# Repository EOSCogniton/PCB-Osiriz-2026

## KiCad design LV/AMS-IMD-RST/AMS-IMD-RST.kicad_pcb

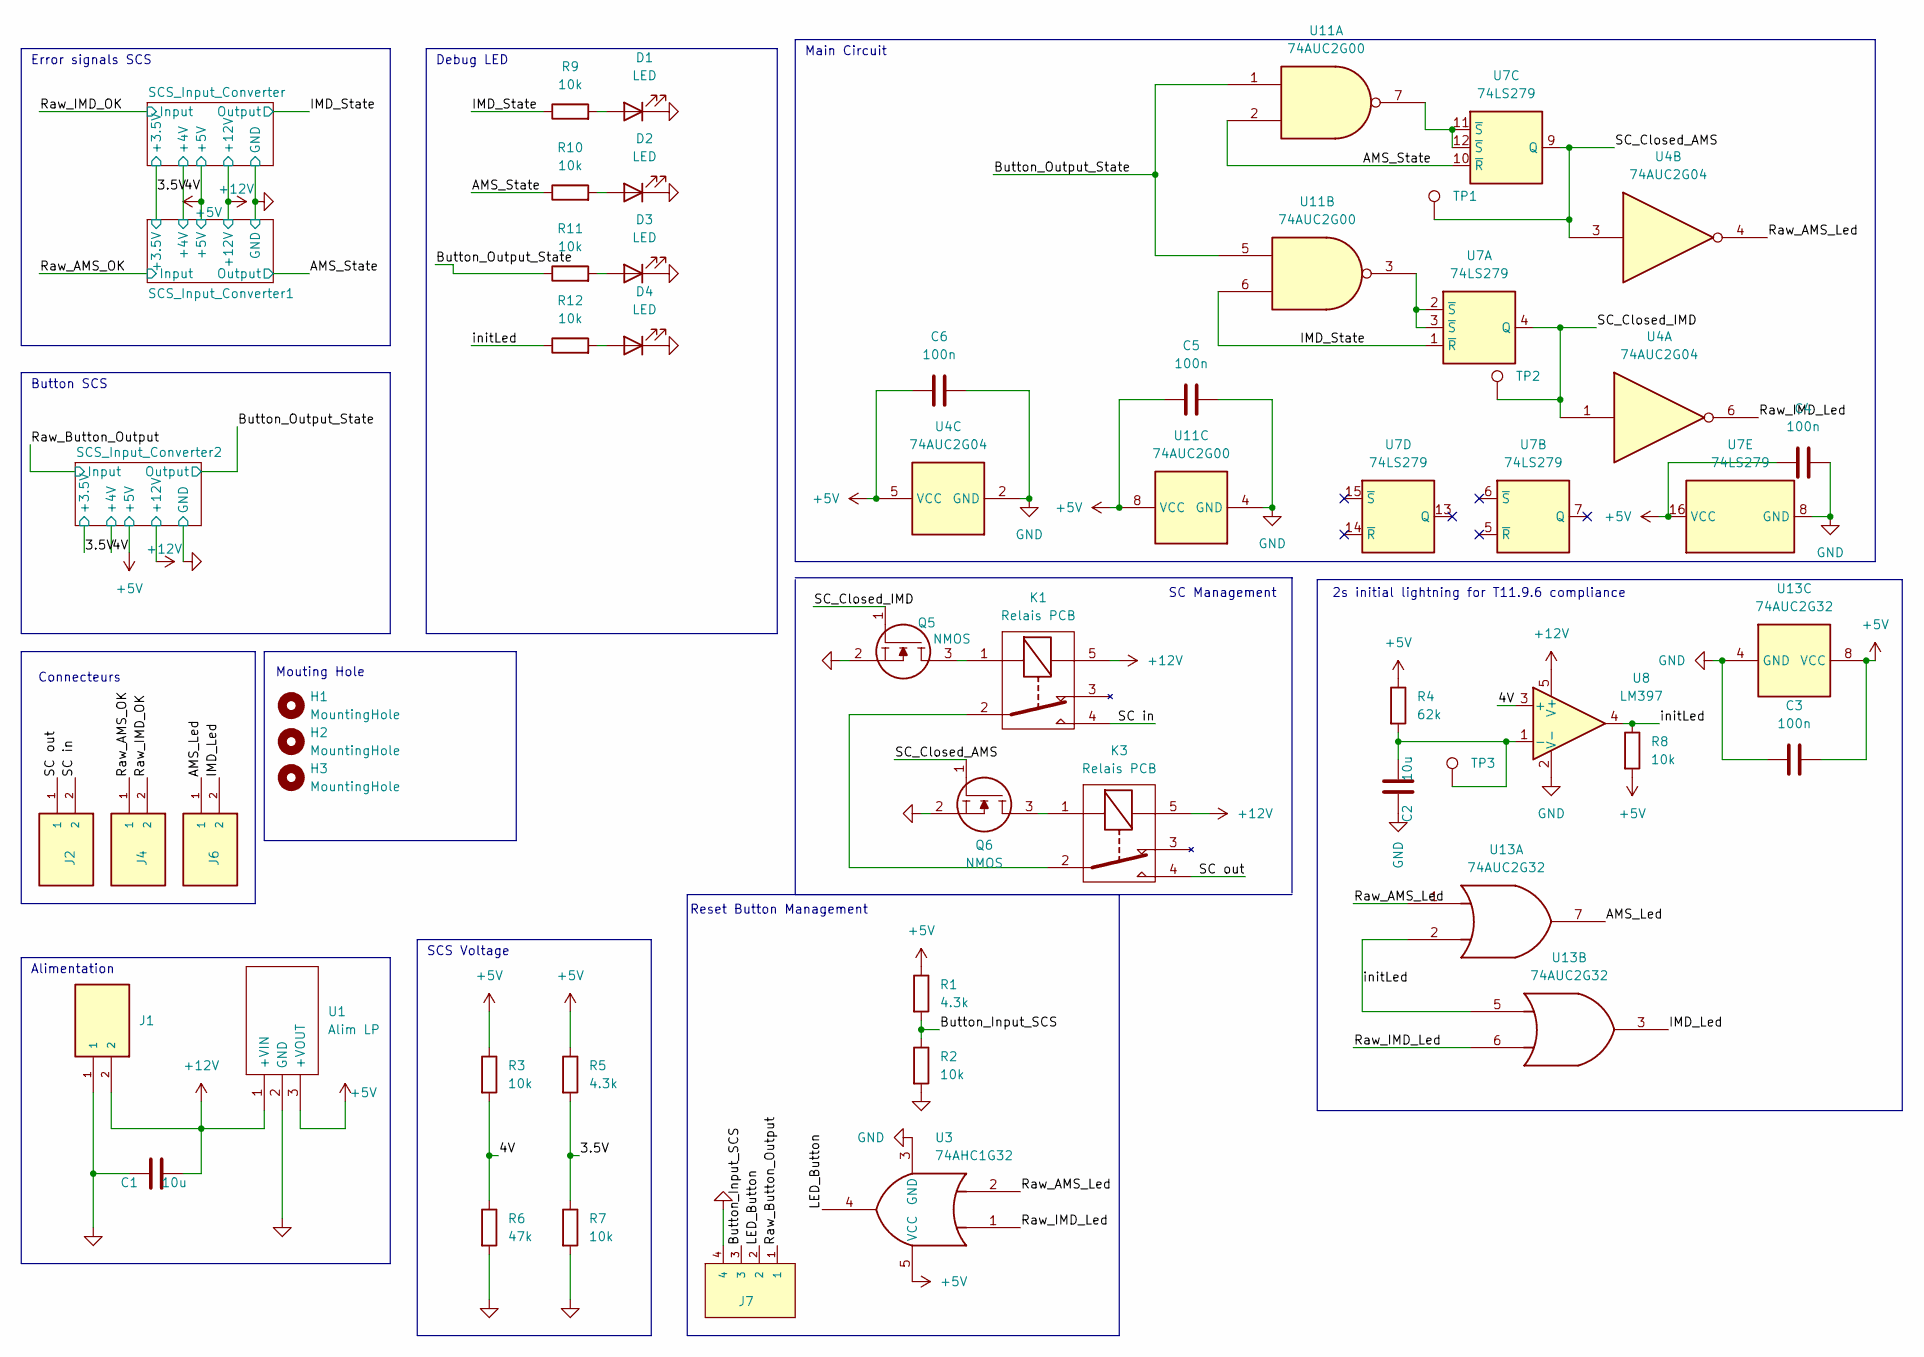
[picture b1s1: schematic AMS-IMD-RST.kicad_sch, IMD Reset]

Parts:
C1, C2: 10u; CP_Radial_D5.0mm_P2.00mm
C3, C4, C5, C6: 100n; C_0805_2012Metric_Pad1.18x1.45mm_HandSolder
D1, D2, D3, D4: LED; LED_D3.0mm
H1, H2, H3: MountingHole; MountingHole_2.7mm_M2.5
J1, J2, J4, J6: 2P Droit 2-11-2022; MOLEX_22-11-2022; PARTREV BD8; Mouser Part Number 538-22-11-2022
J7: 4P Droit 22-11-2042; MOLEX_22-11-2042; Manufacturer_Part_Number 22-11-2042; Mouser Part Number 538-22-11-2042
K1, K3: Relais PCB; CP112V; Mouser Part Number 769-CP1-12V
Q5, Q6: NMOS SQ2348ES-T1_GE3; SOT95P237X112-3N; Manufacturer_Part_Number SQ2348ES-T1_GE3; Mouser Part Number 781-SQ2348ES-T1_GE3
R1, R5: 4.3k; R_0805_2012Metric_Pad1.20x1.40mm_HandSolder
R2, R3, R7, R8, R9, R10, R11, R12: 10k; R_0805_2012Metric_Pad1.20x1.40mm_HandSolder
R4: 62k; R_0805_2012Metric_Pad1.20x1.40mm_HandSolder
R6: 47k; R_0805_2012Metric_Pad1.20x1.40mm_HandSolder
TP1, TP2, TP3: type="R" model="TestPoint" lib=""; TestPoint_Pad_D1.0mm
U1: Alim LP TSR_0.5-2450; TSR-0.5-2433; Manufacturer_Part_Number TSR 0.5-2450; Mouser Part Number 495-TSR0.5-2450
U3: 74AHC1G32; SOT-23-5
U4: 74AUC2G04; SOT-23-6
U7: 74LS279; SOIC-16W_5.3x10.2mm_P1.27mm
U8: LM397; SOT-23-5
U11: 74AUC2G00; SSOP-8_3.9x5.05mm_P1.27mm
U13: 74AUC2G32; SSOP-8_3.9x5.05mm_P1.27mm

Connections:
+5V: C3.2, C4.1, C5.1, C6.1, R1.1, R3.1, R4.1, R5.1, R8.2, U1.3 (+VOUT), U3.5 (VCC), U4.5 (VCC), U7.16 (VCC), U11.8 (VCC), U13.8 (VCC); also elsewhere on the board
+12V: C1.1, J1.2, K1.5, K3.5, U1.1 (+VIN), U8.5 (V+); also elsewhere on the board
/3.5V: R5.2, R7.1; also elsewhere on the board
/4V: R3.2, R6.1, U8.3 (+); also elsewhere on the board
/AMS_Led: J6.1, U13.7
/AMS_State: R10.1, U7.10 (~R), U11.2; also elsewhere on the board
/Button_Input_SCS: J7.3, R1.2, R2.1
/Button_Output_State: R11.1, U11.1, U11.5; also elsewhere on the board
/IMD_Led: J6.2, U13.3
/IMD_State: R9.1, U7.1 (~R), U11.6; also elsewhere on the board
/LED_Button: J7.2, U3.4
/Raw_AMS_Led: U3.2, U4.4, U13.1
/Raw_AMS_OK: J4.1; also elsewhere on the board
/Raw_Button_Output: J7.1; also elsewhere on the board
/Raw_IMD_Led: U3.1, U4.6, U13.6
/Raw_IMD_OK: J4.2; also elsewhere on the board
/SC in: J2.2, K1.4
/SC out: J2.1, K3.4
/SC_Closed_AMS: Q6.1, TP1.1, U4.3, U7.9 (Q)
/SC_Closed_IMD: Q5.1, TP2.1, U4.1, U7.4 (Q)
/initLed: R8.1, R12.1, U8.4, U13.2, U13.5
GND: C1.2, C2.2, C3.1, C4.2, C5.2, C6.2, D1.1 (K), D2.1 (K), D3.1 (K), D4.1 (K), J1.1, J7.4, Q5.2, Q6.2, R2.2, R6.2, R7.2, U1.2 (GND), U3.3 (GND), U4.2 (GND), U7.8 (GND), U8.2 (V-), U11.4 (GND), U13.4 (GND); also elsewhere on the board
unnamed: D1.2 (A), R9.2
unnamed: D2.2 (A), R10.2
unnamed: D3.2 (A), R11.2
unnamed: D4.2 (A), R12.2
unnamed: K1.1, Q5.3
unnamed: K1.2, K3.2
unnamed: K3.1, Q6.3
unnamed: C2.1, R4.2, TP3.1, U8.1 (-)
unnamed: U7.2 (~S), U7.3 (~S), U11.3
unnamed: U7.11 (~S), U7.12 (~S), U11.7

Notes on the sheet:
Error signals SCS
Button SCS
2s initial lightning for T11.9.6 compliance
Debug LED
Alimentation
SC Management
Main Circuit
Mouting Hole
Reset Button Management
SCS Voltage
Connecteurs

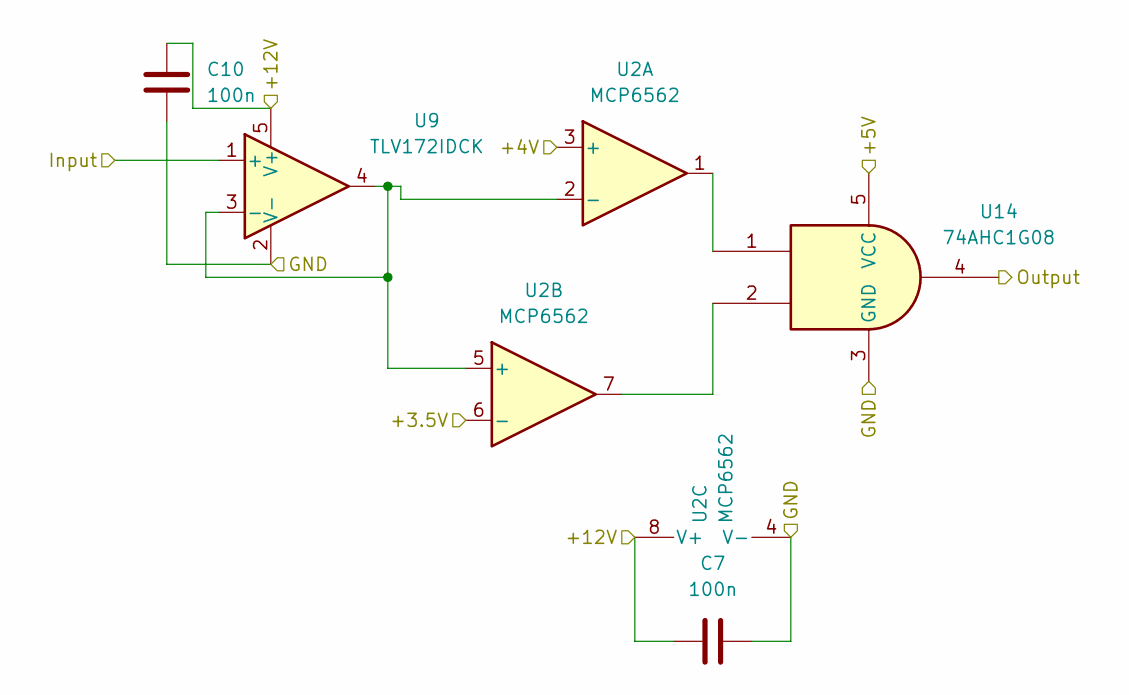
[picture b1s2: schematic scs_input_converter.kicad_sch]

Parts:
C7, C10: 100n; C_0805_2012Metric_Pad1.18x1.45mm_HandSolder
U2: MCP6562; MSOP-8_3x3mm_P0.65mm
U9: TLV172IDCK; SOT-353_SC-70-5
U14: 74AHC1G08; SOT-23-5

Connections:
+5V: U14.5 (VCC); also elsewhere on the board
+12V: C7.1, C10.2, U2.8 (V+), U9.5 (V+); also elsewhere on the board
/3.5V: U2.6 (-); also elsewhere on the board
/4V: U2.3 (+); also elsewhere on the board
/IMD_State: U14.4; also elsewhere on the board
/Raw_IMD_OK: U9.1 (+); also elsewhere on the board
GND: C7.2, C10.1, U2.4 (V-), U9.2 (V-), U14.3 (GND); also elsewhere on the board
unnamed: U2.2 (-), U2.5 (+), U9.3 (-), U9.4
unnamed: U2.1, U14.1
unnamed: U2.7, U14.2

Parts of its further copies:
C8, C9, C11, C12: 100n; C_0805_2012Metric_Pad1.18x1.45mm_HandSolder
U5, U6: MCP6562; MSOP-8_3x3mm_P0.65mm
U10, U17: TLV172IDCK; SOT-353_SC-70-5
U15, U16: 74AHC1G08; SOT-23-5

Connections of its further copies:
+5V: U15.5 (VCC), U16.5 (VCC); also elsewhere on the board
+12V: C8.1, C9.1, C11.2, C12.2, U5.8 (V+), U6.8 (V+), U10.5 (V+), U17.5 (V+); also elsewhere on the board
/3.5V: U5.6 (-), U6.6 (-); also elsewhere on the board
/4V: U5.3 (+), U6.3 (+); also elsewhere on the board
/AMS_State: U15.4; also elsewhere on the board
/Button_Output_State: U16.4; also elsewhere on the board
/Raw_AMS_OK: U10.1 (+); also elsewhere on the board
/Raw_Button_Output: U17.1 (+); also elsewhere on the board
GND: C8.2, C9.2, C11.1, C12.1, U5.4 (V-), U6.4 (V-), U10.2 (V-), U15.3 (GND), U16.3 (GND), U17.2 (V-); also elsewhere on the board
unnamed: U5.2 (-), U5.5 (+), U10.3 (-), U10.4
unnamed: U5.1, U15.1
unnamed: U5.7, U15.2
unnamed: U6.1, U16.1
unnamed: U6.7, U16.2
unnamed: U6.2 (-), U6.5 (+), U17.3 (-), U17.4

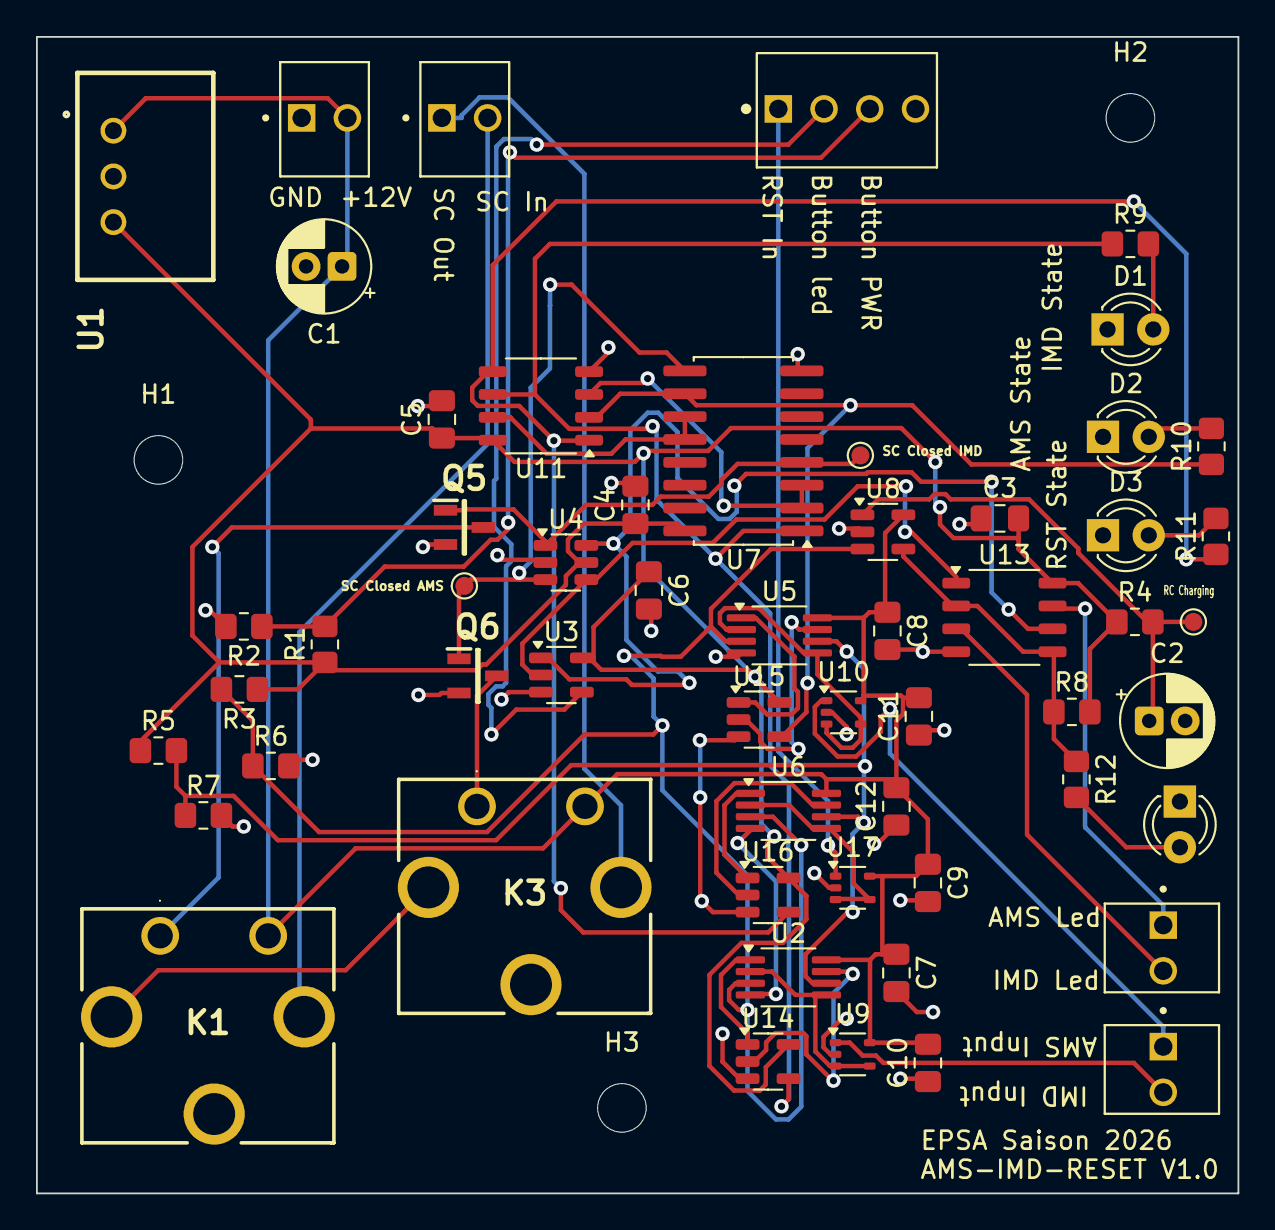
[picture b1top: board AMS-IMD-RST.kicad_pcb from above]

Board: 2 copper layers, 66.8 x 64.2 mm, 59 parts (0 on the bottom side), 41 nets.

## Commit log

2025-10-23 Fist commit and Tractive System update
2025-10-23 AMS-IMD-RST project created
2025-10-26 SCS added
2025-10-27 Add SCS explaination graph
2025-10-27 Finished V1.0 of Schematic and PCB
2025-10-28 Added 2s lightning for T11.9.6 compliance
2025-10-29 Added test LEDS and testpoints on schem
2025-10-29 PCB rooting finished
2025-10-30 Résolution problème AMS IMD RST
